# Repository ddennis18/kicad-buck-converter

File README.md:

# DC-DC Buck Converter

KiCad design for an adjustable, non-isolated step-down DC-DC converter based on the TI LM2596S-ADJ switching regulator.

## Design Overview

- Adjustable output voltage set with RV1 (10 kOhm potentiometer).
- LM2596S-ADJ regulator with an SS34 Schottky catch diode and 47 uH inductor.
- Single-pin 2.54 mm through-hole terminals for input and output.
- Design credit in the schematic: Osemwegie Osemwonken Darius Dennis (D18S).

The LM2596 family is a 3 A regulator, but that is not a guarantee of 3 A continuous output from this board. Usable input/output voltage and current depend on the regulator datasheet limits, component ratings, PCB thermal performance, and cooling. Confirm these limits before use.

## Connections

| Reference | Connection |
| --- | --- |
| J1 | VIN, positive input |
| J2 | GND, input return |
| J3 | VOUT, positive regulated output |
| J4 | GND, output return |

The converter is non-isolated; input and output grounds are common. Check polarity before applying power and verify the output voltage with a meter before connecting a load.

## Project Files

| File | Description |
| --- | --- |
| `buck-converter.kicad_pro` | KiCad project settings |
| `buck-converter.kicad_sch` | Circuit schematic |
| `buck-converter.kicad_pcb` | PCB layout |
| `buck-converter.csv` | Schematic-generated bill of materials |
| `Datasheets/lm2596.pdf` | LM2596 datasheet |

Open `buck-converter.kicad_pro` in KiCad to view or edit the design. The CSV BOM contains the component values, footprints, and an SS34 datasheet link.

## Bring-Up Notes

1. Review the schematic and board layout, and run KiCad electrical-rule and design-rule checks before fabrication or assembly.
2. Confirm component polarity and orientation, especially C2/C3, D1/D2, and U1.
3. Start with a current-limited input supply. Measure VOUT and adjust RV1 before connecting a load.
4. Check regulator, diode, and inductor temperatures under load; reduce load or improve cooling if they become excessive.

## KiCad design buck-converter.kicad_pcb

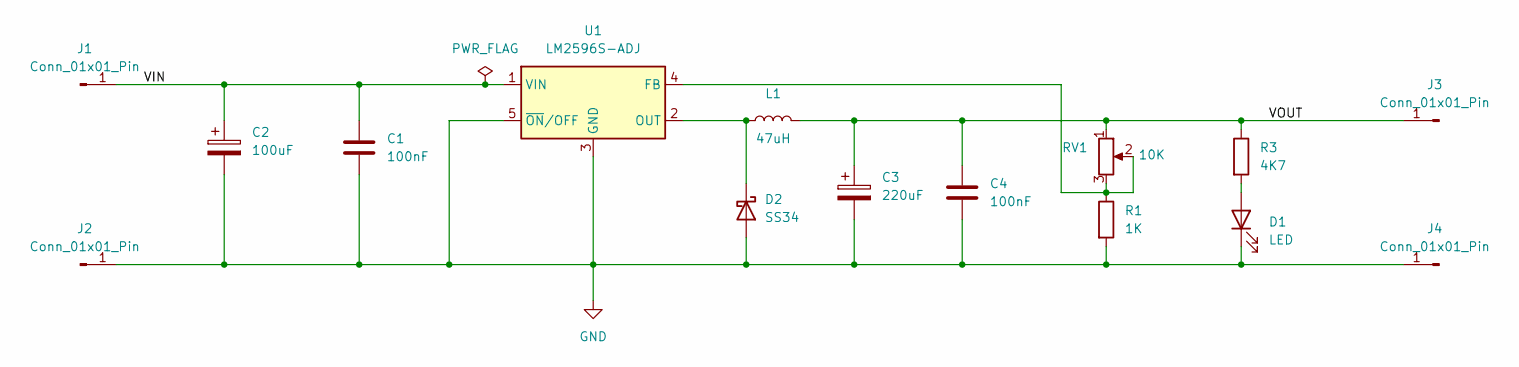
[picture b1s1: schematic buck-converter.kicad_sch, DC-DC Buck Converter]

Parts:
C1, C4: 100nF; C_0603_1608Metric
C2: 100uF; CP_Elec_8x10
C3: 220uF; CP_Elec_8x10
D1: LED; LED_0603_1608Metric
D2: SS34; D_SMA
J1, J2, J3, J4: Conn_01x01_Pin; PinHeader_1x01_P2.54mm_Vertical
L1: 47uH; L_Bourns_SRR1260
R1: 1K; R_0603_1608Metric
R3: 4K7; R_0603_1608Metric
RV1: 10K; Potentiometer_Bourns_3296W_Vertical
U1: LM2596S-ADJ; TO-263-5_TabPin3

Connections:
/VIN: C1.1, C2.1, J1.1 (Pin_1_1), U1.1 (VIN)
/VOUT: C3.1, C4.1, J3.1 (Pin_1_1), L1.2, R3.1, RV1.1
GND: C1.2, C2.2, C3.2, C4.2, D1.1 (K), D2.2 (A), J2.1 (Pin_1_1), J4.1 (Pin_1_1), R1.2, U1.3 (GND), U1.5 (~ON/OFF)
unnamed: D1.2 (A), R3.2
unnamed: D2.1 (K), L1.1, U1.2 (OUT)
unnamed: R1.1, RV1.2, RV1.3, U1.4 (FB)

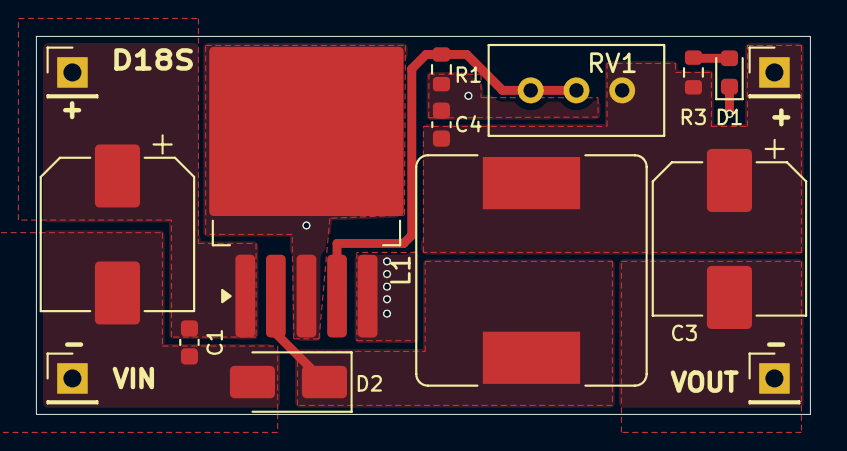
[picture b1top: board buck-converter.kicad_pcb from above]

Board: 2 copper layers, 43.0 x 21.0 mm, 15 parts (0 on the bottom side), 6 nets.
